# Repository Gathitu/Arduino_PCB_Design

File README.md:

A pdf containing the Printed Circuit Board's (PCB) Design Schematic:
[Schematic_PDF](/Arduino_PCB_Design/Schematic_PDF/Arduino_PCB_Design.pdf)

**Snips of the PCB's views:**

Side View

Top View

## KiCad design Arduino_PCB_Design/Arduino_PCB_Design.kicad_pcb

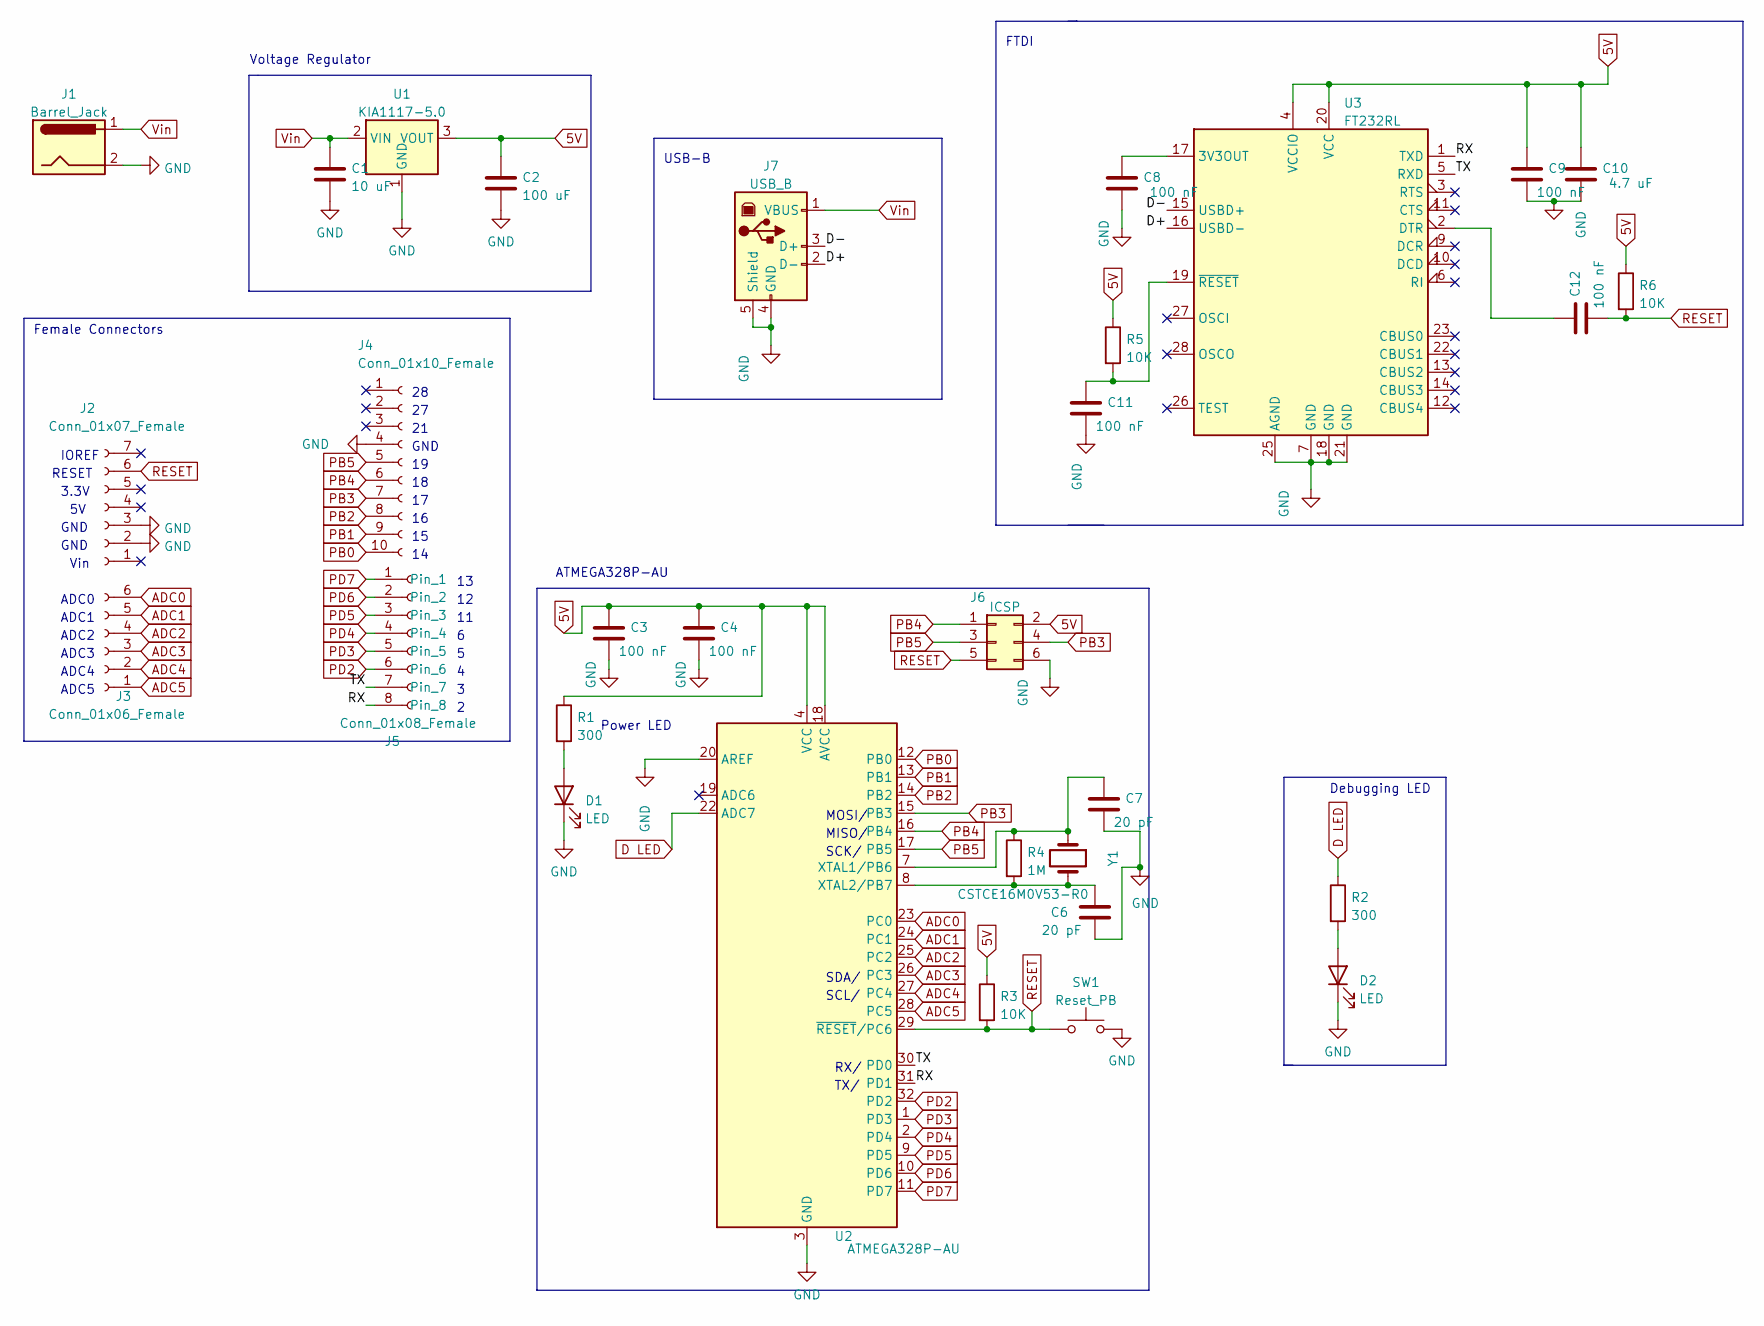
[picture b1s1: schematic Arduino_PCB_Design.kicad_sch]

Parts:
C1: 10 uF; C_0603_1608Metric
C2: 100 uF; C_0603_1608Metric
C3, C4, C8, C9, C11, C12: 100 nF; C_0603_1608Metric
C6, C7: 20 pF; C_0603_1608Metric
C10: 4.7 uF; C_0603_1608Metric
D1, D2: LED; LED_0603_1608Metric
J1: Barrel_Jack; BarrelJack_CUI_PJ-063AH_Horizontal
J2: Conn_01x07_Female; PinSocket_1x07_P2.54mm_Vertical_SMD_Pin1Left
J3: Conn_01x06_Female; PinSocket_1x06_P2.54mm_Vertical_SMD_Pin1Left
J4: Conn_01x10_Female; PinSocket_1x10_P2.54mm_Vertical_SMD_Pin1Right
J5: Conn_01x08_Female; PinSocket_1x08_P2.54mm_Vertical_SMD_Pin1Right
J6: ICSP; PinHeader_2x03_P2.54mm_Vertical_SMD
J7: USB_B; USB_Mini-B_Lumberg_2486_01_Horizontal
R1, R2: 300; R_0603_1608Metric
R3, R5, R6: 10K; R_0603_1608Metric
R4: 1M; R_0603_1608Metric
SW1: Reset_PB; SW_SPST_B3U-1000P
U1: KIA1117-5.0; SOT-89-3
U2: ATMEGA328P-AU; TQFP-32_7x7mm_P0.8mm
U3: FT232RL; SSOP-28_5.3x10.2mm_P0.65mm
Y1: CSTCE16M0V53-R0; Crystal_SMD_0603-2Pin_6.0x3.5mm

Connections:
5V: C2.1, C3.1, C4.1, C9.1, C10.1, J6.2, R1.1, R3.1, R5.1, R6.1, U1.3 (VOUT), U2.4 (VCC), U2.6 (VCC), U2.18 (AVCC), U3.4 (VCCIO), U3.20 (VCC); also elsewhere on the board
/D+: J7.2 (D-), U3.16 (USBD-)
/D-: J7.3 (D+), U3.15 (USBD+)
/RX: J5.8, U2.31 (PD1), U3.1 (TXD)
/TX: J5.7, U2.30 (PD0), U3.5 (RXD)
ADC0: J3.6, U2.23 (PC0)
ADC1: J3.5, U2.24 (PC1)
ADC2: J3.4, U2.25 (PC2)
ADC3: J3.3, U2.26 (PC3)
ADC4: J3.2, U2.27 (PC4)
ADC5: J3.1, U2.28 (PC5)
D LED: R2.1, U2.22 (ADC7)
GND: C1.2, C2.2, C3.2, C4.2, C6.2, C7.2, C8.2, C9.2, C10.2, C11.2, D1.1 (K), D2.1 (K), J1.2, J2.2, J2.3, J4.4, J6.6, J7.4 (GND), J7.5 (Shield), SW1.2, U1.1 (GND), U2.3 (GND), U2.5 (GND), U2.20 (AREF), U2.21 (GND), U3.7 (GND), U3.18 (GND), U3.21 (GND), U3.25 (AGND); also elsewhere on the board
unnamed: C6.1, R4.2, U2.8 (XTAL2/PB7), Y1.2
unnamed: C7.1, R4.1, U2.7 (XTAL1/PB6), Y1.1
unnamed: C8.1, U3.17 (3V3OUT)
unnamed: C11.1, R5.2, U3.19 (~RESET)
unnamed: C12.1, U3.2 (DTR)
unnamed: D1.2 (A), R1.2
unnamed: D2.2 (A), R2.2
PB0: J4.10, U2.12 (PB0)
PB1: J4.9, U2.13 (PB1)
PB2: J4.8, U2.14 (PB2)
PB3: J4.7, J6.4, U2.15 (PB3)
PB4: J4.6, J6.1, U2.16 (PB4)
PB5: J4.5, J6.3, U2.17 (PB5)
PD2: J5.6, U2.32 (PD2)
PD3: J5.5, U2.1 (PD3)
PD4: J5.4, U2.2 (PD4)
PD5: J5.3, U2.9 (PD5)
PD6: J5.2, U2.10 (PD6)
PD7: J5.1, U2.11 (PD7)
RESET: C12.2, J2.6, J6.5, R3.2, R6.2, SW1.1, U2.29 (~RESET/PC6)
Vin: C1.1, J1.1, J7.1 (VBUS), U1.2 (VIN)

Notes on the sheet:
SCL/
ADC5
IOREF
Debugging LED
USB-B
SDA/
FTDI
GND
Female Connectors
Vin
ADC4
Power LED
ADC3
ADC2
Voltage Regulator
ADC1
MISO/
RESET
GND
RX/
ADC0
SCK/
MOSI/
3.3V
TX/
ATMEGA328P-AU

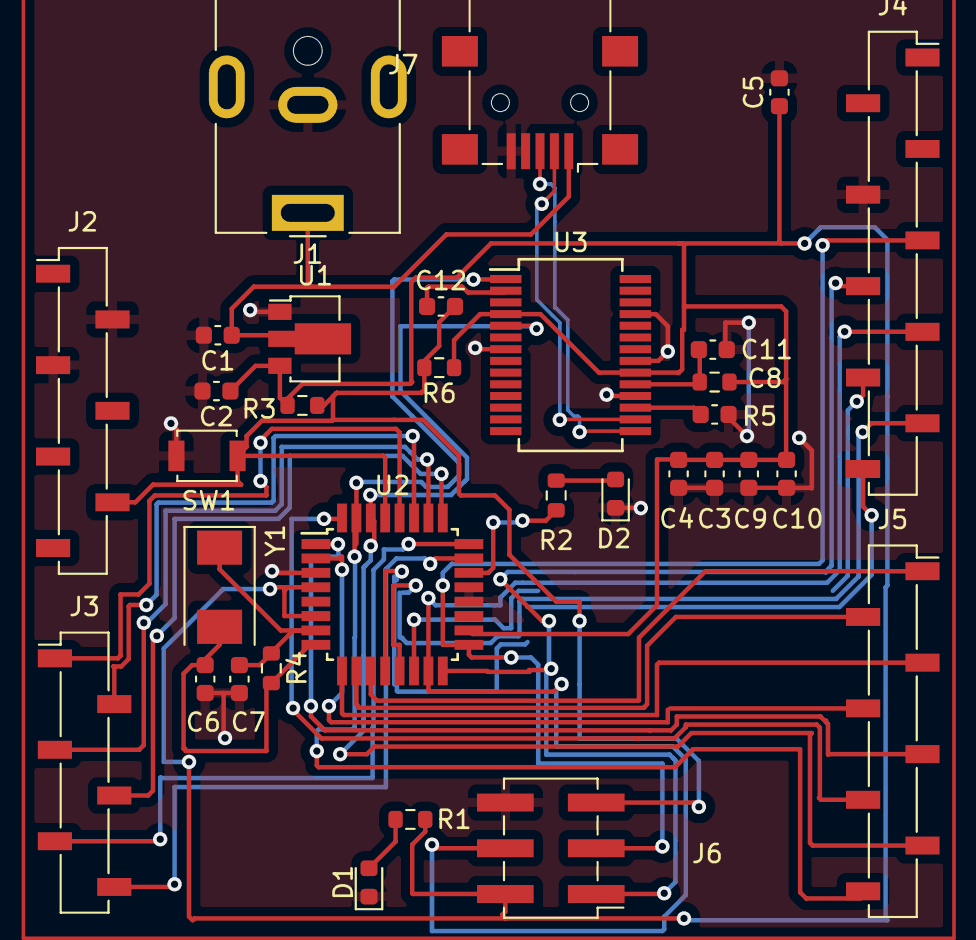
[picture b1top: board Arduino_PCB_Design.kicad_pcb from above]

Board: 2 copper layers, 32 parts (0 on the bottom side), 34 nets.

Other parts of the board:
C5: 100 nF; C_0603_1608Metric

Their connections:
5V: C5.1; also elsewhere on the board
GND: C5.2; also elsewhere on the board

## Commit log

2022-11-12 12/11/2022
